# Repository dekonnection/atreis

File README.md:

# Atreis keyboard

Unsplitting the Iris keyboard.

Based on [Keebio's Iris keyboard design files](https://github.com/keebio/iris-case),
modified to achieve the same layout in a single-piece form-factor.

For more pictures, [the full album is on imgur](https://imgur.com/a/LmST29r).

## Why ?

Because the Iris is perfect, but a splitted keyboard is not the most convenient
keyboard to take when on the go.

And because we can.

## Why this name ?

Because it looks a lot like the [Atreus](https://github.com/technomancy/atreus) keyboard, but with the Iris layout.

## How do I build one ?

Two solutions:
- like I did when I started the project, laser-cut the plates and hand-wire it.
- use the PCB and case files available in this repository, wonderfully created by https://github.com/climent

# Firmware

This keyboard runs under the wonderful [QMK](https://github.com/qmk/qmk_firmware) firmware, my current (preliminary and pretty basic, but functional) code is here : https://github.com/dekonnection/qmk_firmware/tree/master/keyboards/atreis

I will eventually do a merge request in upstream QMK.

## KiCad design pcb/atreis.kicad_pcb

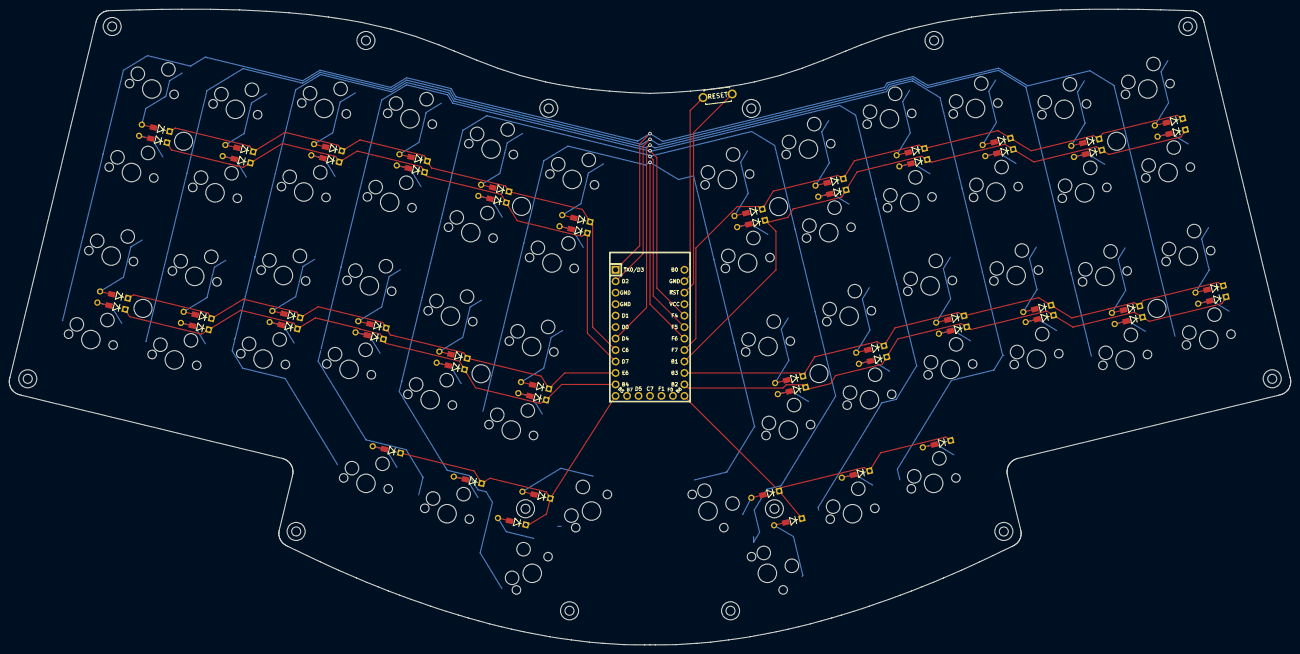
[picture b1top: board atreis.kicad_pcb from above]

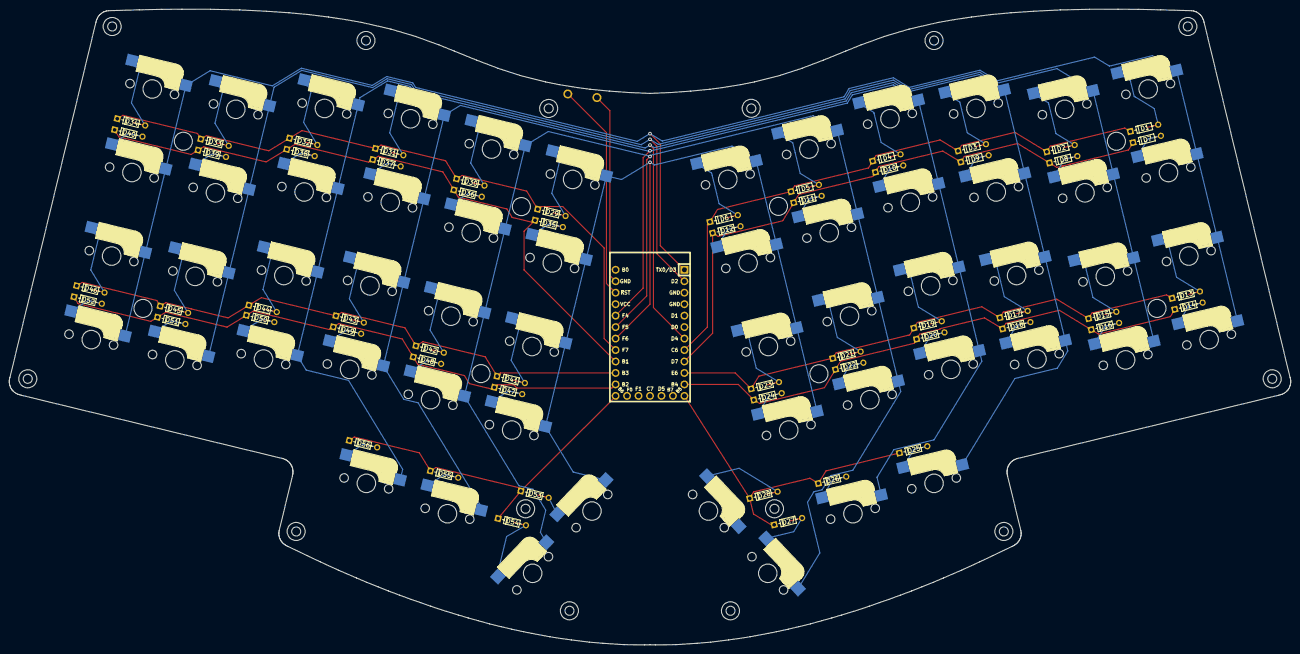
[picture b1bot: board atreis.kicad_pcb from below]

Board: 2 copper layers, 284.0 x 140.8 mm, 114 parts (56 on the bottom side), 74 nets.

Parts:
D1, D2, D3, D4, D5, D6, D7, D8, D9, D10, D11, D12, D13, D14, D15, D16, D17, D18, D19, D20, D21, D22, D23, D24, D25, D26, D27, D28, D29, D30, D31, D32, D33, D34, D35, D36, D37, D38, D39, D40, D41, D42, D43, D44, D45, D46, D47, D48, D49, D50, D51, D52, D53, D54, D55, D56: D_Small; D3_hybrid_common_hole
MX1, MX2, MX3, MX4, MX5, MX6, MX7, MX8, MX9, MX10, MX11, MX12, MX13, MX14, MX15, MX16, MX17, MX18, MX19, MX20, MX21, MX22, MX23, MX24, MX25, MX26, MX27, MX28, MX29, MX30, MX31, MX32, MX33, MX34, MX35, MX36, MX37, MX38, MX39, MX40, MX41, MX42, MX43, MX44, MX45, MX46, MX47, MX48, MX49, MX50, MX51, MX52, MX53, MX54, MX55, MX56: MX-NoLED; CherryMX_Hotswap
SW1: SW_Push; ResetSW_1side
U1: Elite-C

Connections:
COL0: MX1.1 (COL), MX7.1 (COL), MX13.1 (COL), MX19.1 (COL), MX34.1 (COL), MX40.1 (COL), MX46.1 (COL), MX52.1 (COL), U1.1 (TX0/PD3)
COL1: MX2.1 (COL), MX8.1 (COL), MX14.1 (COL), MX20.1 (COL), MX33.1 (COL), MX39.1 (COL), MX45.1 (COL), MX51.1 (COL), U1.2 (RX1/PD2)
COL2: MX3.1 (COL), MX9.1 (COL), MX15.1 (COL), MX21.1 (COL), MX25.1 (COL), MX32.1 (COL), MX38.1 (COL), MX44.1 (COL), MX50.1 (COL), MX56.1 (COL), U1.7 (4/PD4)
COL3: MX4.1 (COL), MX10.1 (COL), MX16.1 (COL), MX22.1 (COL), MX26.1 (COL), MX31.1 (COL), MX37.1 (COL), MX43.1 (COL), MX49.1 (COL), MX55.1 (COL), U1.20 (A3/PF4)
COL4: MX5.1 (COL), MX11.1 (COL), MX17.1 (COL), MX23.1 (COL), MX27.1 (COL), MX30.1 (COL), MX36.1 (COL), MX42.1 (COL), MX48.1 (COL), MX54.1 (COL), U1.19 (A2/PF5)
COL5: MX6.1 (COL), MX12.1 (COL), MX18.1 (COL), MX24.1 (COL), MX28.1 (COL), MX29.1 (COL), MX35.1 (COL), MX41.1 (COL), MX47.1 (COL), MX53.1 (COL), U1.18 (A1/PF6)
GND: SW1.2, U1.3 (GND), U1.4 (GND), U1.23 (GND)
unnamed: D1.2 (A), MX1.2 (ROW)
unnamed: D2.2 (A), MX2.2 (ROW)
unnamed: D3.2 (A), MX3.2 (ROW)
unnamed: D4.2 (A), MX4.2 (ROW)
unnamed: D5.2 (A), MX5.2 (ROW)
unnamed: D6.2 (A), MX6.2 (ROW)
unnamed: D7.2 (A), MX7.2 (ROW)
unnamed: D8.2 (A), MX8.2 (ROW)
unnamed: D9.2 (A), MX9.2 (ROW)
unnamed: D10.2 (A), MX10.2 (ROW)
unnamed: D11.2 (A), MX11.2 (ROW)
unnamed: D12.2 (A), MX12.2 (ROW)
unnamed: D13.2 (A), MX13.2 (ROW)
unnamed: D15.2 (A), MX14.2 (ROW)
unnamed: D17.2 (A), MX15.2 (ROW)
unnamed: D19.2 (A), MX16.2 (ROW)
unnamed: D21.2 (A), MX17.2 (ROW)
unnamed: D23.2 (A), MX18.2 (ROW)
unnamed: D14.2 (A), MX19.2 (ROW)
unnamed: D16.2 (A), MX20.2 (ROW)
unnamed: D18.2 (A), MX21.2 (ROW)
unnamed: D20.2 (A), MX22.2 (ROW)
unnamed: D22.2 (A), MX23.2 (ROW)
unnamed: D24.2 (A), MX24.2 (ROW)
unnamed: D25.2 (A), MX25.2 (ROW)
unnamed: D26.2 (A), MX26.2 (ROW)
unnamed: D27.2 (A), MX27.2 (ROW)
unnamed: D28.2 (A), MX28.2 (ROW)
unnamed: D29.2 (A), MX29.2 (ROW)
unnamed: D30.2 (A), MX30.2 (ROW)
unnamed: D31.2 (A), MX31.2 (ROW)
unnamed: D32.2 (A), MX32.2 (ROW)
unnamed: D33.2 (A), MX33.2 (ROW)
unnamed: D34.2 (A), MX34.2 (ROW)
unnamed: D35.2 (A), MX35.2 (ROW)
unnamed: D36.2 (A), MX36.2 (ROW)
unnamed: D37.2 (A), MX37.2 (ROW)
unnamed: D38.2 (A), MX38.2 (ROW)
unnamed: D39.2 (A), MX39.2 (ROW)
unnamed: D40.2 (A), MX40.2 (ROW)
unnamed: D41.2 (A), MX41.2 (ROW)
unnamed: D42.2 (A), MX42.2 (ROW)
unnamed: D43.2 (A), MX43.2 (ROW)
unnamed: D44.2 (A), MX44.2 (ROW)
unnamed: D45.2 (A), MX45.2 (ROW)
unnamed: D46.2 (A), MX46.2 (ROW)
unnamed: D47.2 (A), MX47.2 (ROW)
unnamed: D48.2 (A), MX48.2 (ROW)
unnamed: D49.2 (A), MX49.2 (ROW)
unnamed: D50.2 (A), MX50.2 (ROW)
unnamed: D51.2 (A), MX51.2 (ROW)
unnamed: D52.2 (A), MX52.2 (ROW)
unnamed: D53.2 (A), MX53.2 (ROW)
unnamed: D54.2 (A), MX54.2 (ROW)
unnamed: D55.2 (A), MX55.2 (ROW)
unnamed: D56.2 (A), MX56.2 (ROW)
unnamed: SW1.1, U1.22 (RST)
ROW0: D1.1 (K), D2.1 (K), D3.1 (K), D4.1 (K), D5.1 (K), D6.1 (K), U1.8 (5/PC6)
ROW1: D7.1 (K), D8.1 (K), D9.1 (K), D10.1 (K), D11.1 (K), D12.1 (K), U1.9 (6/PD7)
ROW2: D13.1 (K), D15.1 (K), D17.1 (K), D19.1 (K), D21.1 (K), D23.1 (K), U1.10 (7/PE6)
ROW3: D14.1 (K), D16.1 (K), D18.1 (K), D20.1 (K), D22.1 (K), D24.1 (K), U1.11 (8/PB4)
ROW4: D25.1 (K), D26.1 (K), D27.1 (K), D28.1 (K), U1.12 (9/PB5)
ROW5: D29.1 (K), D30.1 (K), D31.1 (K), D32.1 (K), D33.1 (K), D34.1 (K), U1.17 (A0/PF7)
ROW6: D35.1 (K), D36.1 (K), D37.1 (K), D38.1 (K), D39.1 (K), D40.1 (K), U1.16 (15/PB1)
ROW7: D41.1 (K), D42.1 (K), D43.1 (K), D44.1 (K), D45.1 (K), D46.1 (K), U1.15 (14/PB3)
ROW8: D47.1 (K), D48.1 (K), D49.1 (K), D50.1 (K), D51.1 (K), D52.1 (K), U1.14 (16/PB2)
ROW9: D53.1 (K), D54.1 (K), D55.1 (K), D56.1 (K), U1.13 (10/PB6)

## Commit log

2018-01-21 add initial README
2018-01-21 README : add name explanation
2018-01-21 add initial case files
2018-01-21 fix word
2018-01-21 add license file
2018-05-03 Add link to code in README.
2018-05-03 Add a picture to the README
2018-05-03 Add link to imgur full album
2022-01-01 Initial PCB files.
2022-01-02 Completed tracks and edge. Cleaned up drawings.
2022-01-02 Completed upper case.
2022-01-02 Added images.
2022-01-03 Updated tracks that were too close to the holes.
2022-01-03 mention PCB availability in README
2022-01-03 Completed PCB work. Few improvements may come along, if there is any interest. (#3)
    Add PCB and case files
2022-01-06 Added gerber files. Removed target from PCB.
2022-01-08 Added bottom side of the case. Rerouted some tracks to make space for the holes in the middle of the PCB. Added holes to the top case.
2022-01-08 Rerouted some of the tracks. Much nicer now. Rerouted tracks to make the holes thru holes, to use with spacers. Re-generated gerber file.
